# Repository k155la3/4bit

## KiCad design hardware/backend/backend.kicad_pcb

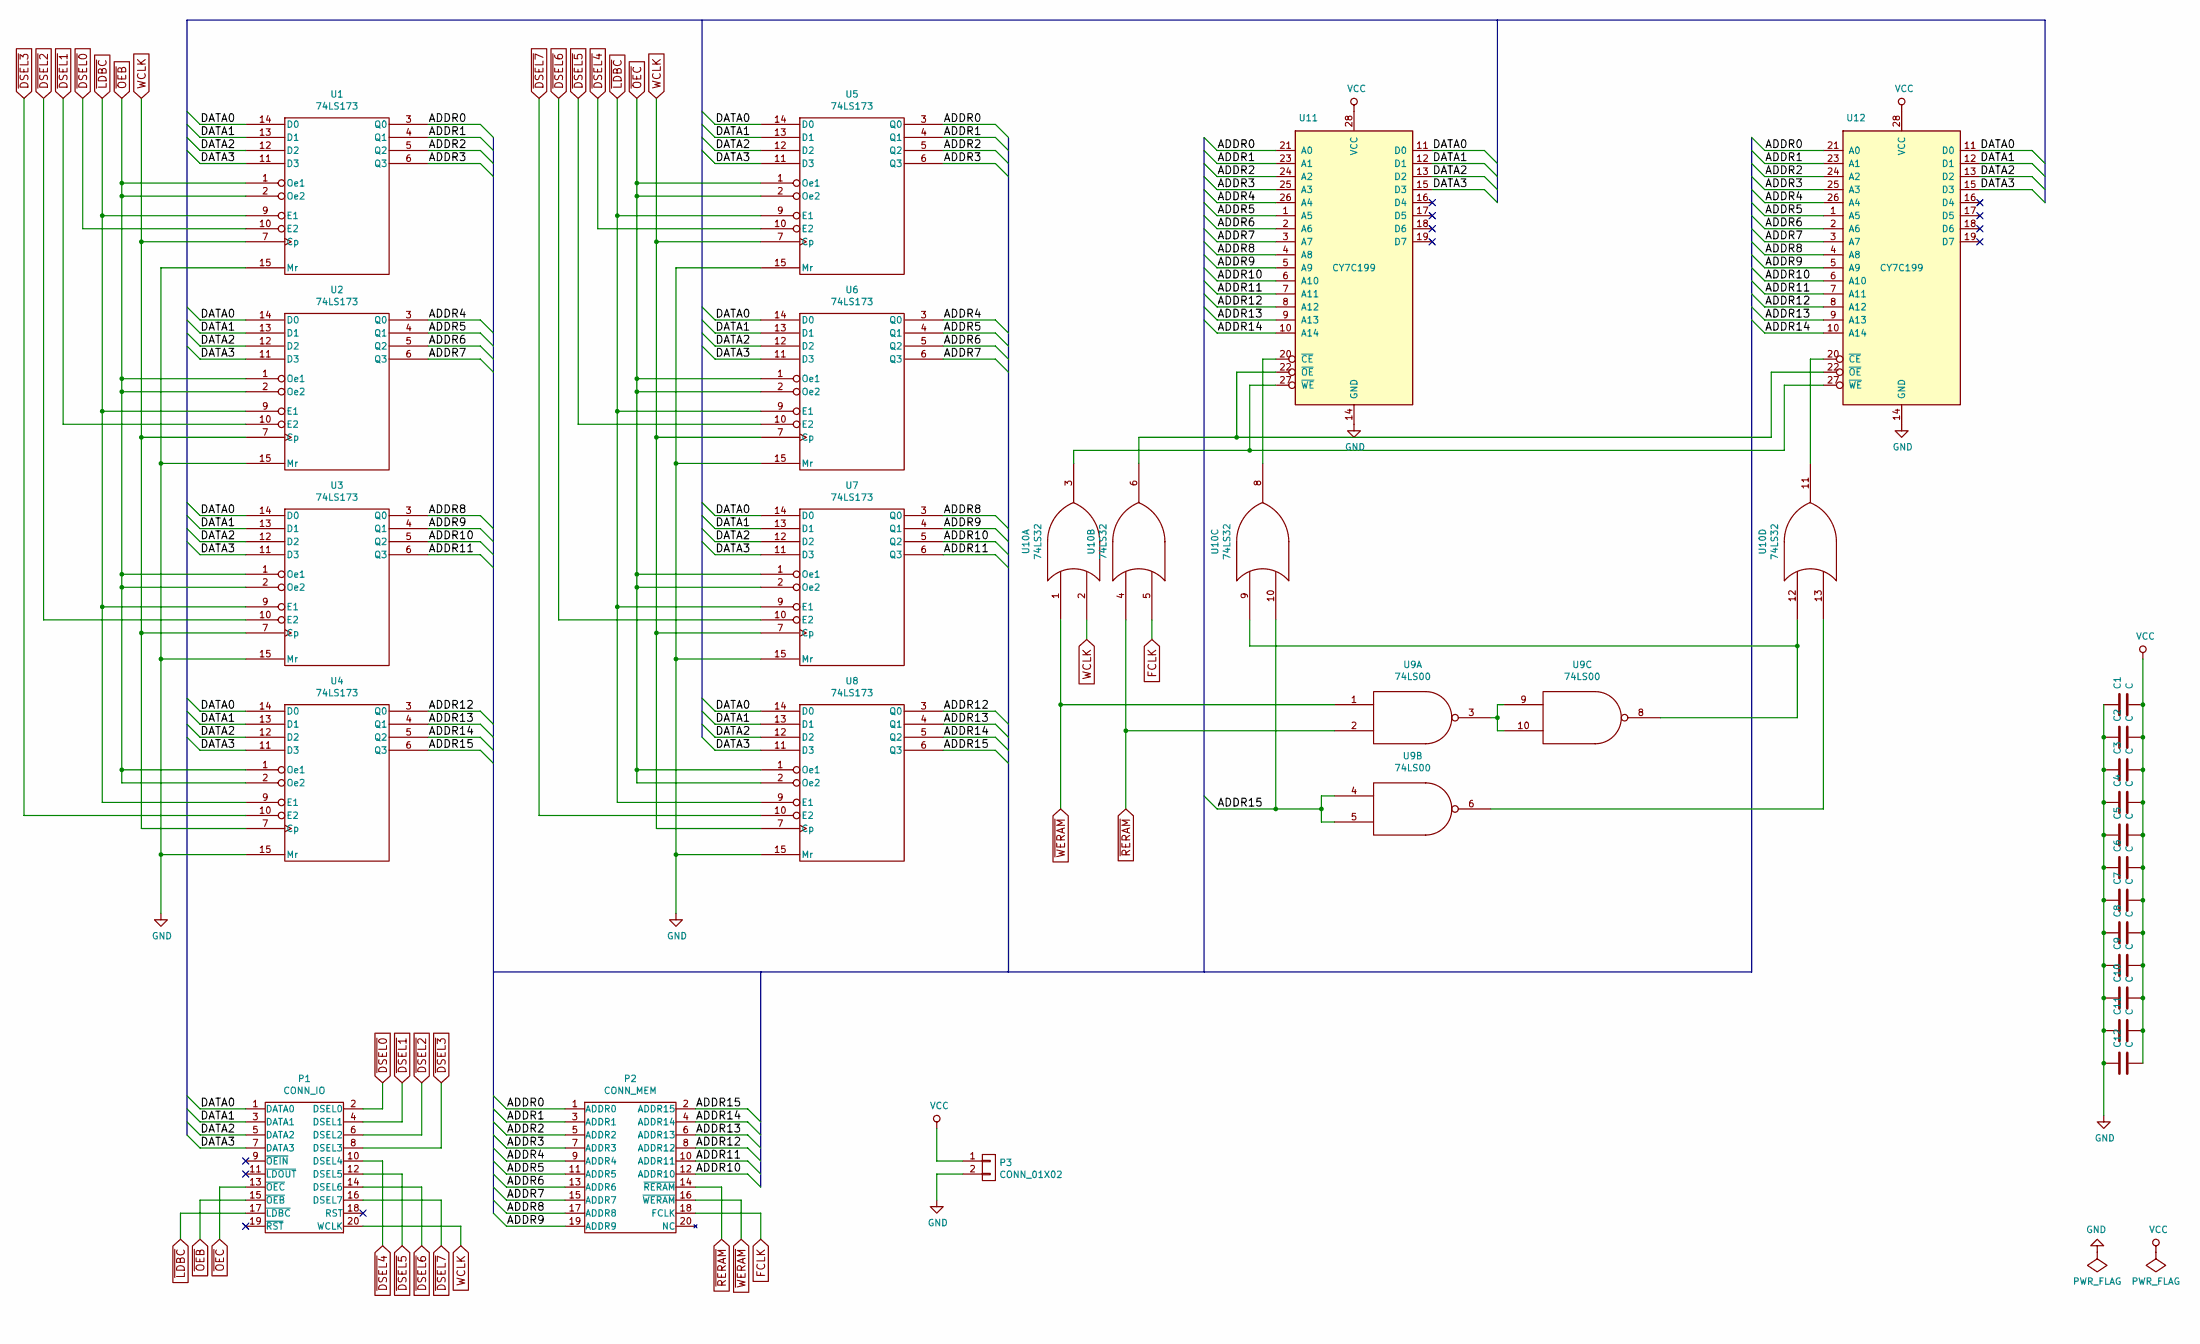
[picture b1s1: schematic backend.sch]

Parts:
C1, C2, C3, C4, C5, C6, C7, C8, C9, C10, C11, C12: C; C_Disc_D3_P2.5
P1: CONN_IO; Socket_Strip_Straight_2x10
P2: CONN_MEM; Socket_Strip_Straight_2x10
P3: CONN_01X02; Pin_Header_Straight_1x02
U1, U2, U3, U4, U5, U6, U7, U8: 74LS173; DIP-16_W7.62mm
U9: 74LS00; DIP-14_W7.62mm
U10: 74LS32; DIP-14_W7.62mm
U11, U12: CY7C199; DIP-28_W7.62mm

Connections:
/ADDR0: P2.1 (ADDR0), U1.3 (Q0), U5.3 (Q0), U11.21 (A0), U12.21 (A0)
/ADDR1: P2.3 (ADDR1), U1.4 (Q1), U5.4 (Q1), U11.23 (A1), U12.23 (A1)
/ADDR2: P2.5 (ADDR2), U1.5 (Q2), U5.5 (Q2), U11.24 (A2), U12.24 (A2)
/ADDR3: P2.7 (ADDR3), U1.6 (Q3), U5.6 (Q3), U11.25 (A3), U12.25 (A3)
/ADDR4: P2.9 (ADDR4), U2.3 (Q0), U6.3 (Q0), U11.26 (A4), U12.26 (A4)
/ADDR5: P2.11 (ADDR5), U2.4 (Q1), U6.4 (Q1), U11.1 (A5), U12.1 (A5)
/ADDR6: P2.13 (ADDR6), U2.5 (Q2), U6.5 (Q2), U11.2 (A6), U12.2 (A6)
/ADDR7: P2.15 (ADDR7), U2.6 (Q3), U6.6 (Q3), U11.3 (A7), U12.3 (A7)
/ADDR8: P2.17 (ADDR8), U3.3 (Q0), U7.3 (Q0), U11.4 (A8), U12.4 (A8)
/ADDR9: P2.19 (ADDR9), U3.4 (Q1), U7.4 (Q1), U11.5 (A9), U12.5 (A9)
/ADDR10: P2.12 (ADDR10), U3.5 (Q2), U7.5 (Q2), U11.6 (A10), U12.6 (A10)
/ADDR11: P2.10 (ADDR11), U3.6 (Q3), U7.6 (Q3), U11.7 (A11), U12.7 (A11)
/ADDR12: P2.8 (ADDR12), U4.3 (Q0), U8.3 (Q0), U11.8 (A12), U12.8 (A12)
/ADDR13: P2.6 (ADDR13), U4.4 (Q1), U8.4 (Q1), U11.9 (A13), U12.9 (A13)
/ADDR14: P2.4 (ADDR14), U4.5 (Q2), U8.5 (Q2), U11.10 (A14), U12.10 (A14)
/ADDR15: P2.2 (ADDR15), U4.6 (Q3), U8.6 (Q3), U9.4, U9.5, U10.10
/DATA0: P1.1 (DATA0), U1.14 (D0), U2.14 (D0), U3.14 (D0), U4.14 (D0), U5.14 (D0), U6.14 (D0), U7.14 (D0), U8.14 (D0), U11.11 (D0), U12.11 (D0)
/DATA1: P1.3 (DATA1), U1.13 (D1), U2.13 (D1), U3.13 (D1), U4.13 (D1), U5.13 (D1), U6.13 (D1), U7.13 (D1), U8.13 (D1), U11.12 (D1), U12.12 (D1)
/DATA2: P1.5 (DATA2), U1.12 (D2), U2.12 (D2), U3.12 (D2), U4.12 (D2), U5.12 (D2), U6.12 (D2), U7.12 (D2), U8.12 (D2), U11.13 (D2), U12.13 (D2)
/DATA3: P1.7 (DATA3), U1.11 (D3), U2.11 (D3), U3.11 (D3), U4.11 (D3), U5.11 (D3), U6.11 (D3), U7.11 (D3), U8.11 (D3), U11.15 (D3), U12.15 (D3)
FCLK: P2.18 (FCLK), U10.5
GND: C1.1, C2.1, C3.1, C4.1, C5.1, C6.1, C7.1, C8.1, C9.1, C10.1, C11.1, C12.1, P3.2, U1.8 (GND), U1.15 (Mr), U2.8 (GND), U2.15 (Mr), U3.8 (GND), U3.15 (Mr), U4.8 (GND), U4.15 (Mr), U5.8 (GND), U5.15 (Mr), U6.8 (GND), U6.15 (Mr), U7.8 (GND), U7.15 (Mr), U8.8 (GND), U8.15 (Mr), U9.7 (GND), U10.7 (GND), U11.14 (GND), U12.14 (GND)
unnamed: U9.3, U9.9, U9.10
unnamed: U10.3, U11.27 (~WE~), U12.27 (~WE~)
unnamed: U10.6, U11.22 (~OE~), U12.22 (~OE~)
unnamed: U10.8, U11.20 (~CE~)
unnamed: U10.11, U12.20 (~CE~)
unnamed: U9.8, U10.9, U10.12
unnamed: U9.6, U10.13
VCC: C1.2, C2.2, C3.2, C4.2, C5.2, C6.2, C7.2, C8.2, C9.2, C10.2, C11.2, C12.2, P3.1, U1.16 (VCC), U2.16 (VCC), U3.16 (VCC), U4.16 (VCC), U5.16 (VCC), U6.16 (VCC), U7.16 (VCC), U8.16 (VCC), U9.14 (VCC), U10.14 (VCC), U11.28 (VCC), U12.28 (VCC)
WCLK: P1.20 (WCLK), U1.7 (Cp), U2.7 (Cp), U3.7 (Cp), U4.7 (Cp), U5.7 (Cp), U6.7 (Cp), U7.7 (Cp), U8.7 (Cp), U10.2
~DSEL0: P1.2 (DSEL0), U1.10 (E2)
~DSEL1: P1.4 (DSEL1), U2.10 (E2)
~DSEL2: P1.6 (DSEL2), U3.10 (E2)
~DSEL3: P1.8 (DSEL3), U4.10 (E2)
~DSEL4: P1.10 (DSEL4), U5.10 (E2)
~DSEL5: P1.12 (DSEL5), U6.10 (E2)
~DSEL6: P1.14 (DSEL6), U7.10 (E2)
~DSEL7: P1.16 (DSEL7), U8.10 (E2)
~LDBC: P1.17 (~LDBC), U1.9 (E1), U2.9 (E1), U3.9 (E1), U4.9 (E1), U5.9 (E1), U6.9 (E1), U7.9 (E1), U8.9 (E1)
~OEB: P1.15 (~OEB), U1.1 (Oe1), U1.2 (Oe2), U2.1 (Oe1), U2.2 (Oe2), U3.1 (Oe1), U3.2 (Oe2), U4.1 (Oe1), U4.2 (Oe2)
~OEC: P1.13 (~OEC), U5.1 (Oe1), U5.2 (Oe2), U6.1 (Oe1), U6.2 (Oe2), U7.1 (Oe1), U7.2 (Oe2), U8.1 (Oe1), U8.2 (Oe2)
~RERAM: P2.14 (~RERAM), U9.2, U10.4
~WERAM: P2.16 (~WERAM), U9.1, U10.1

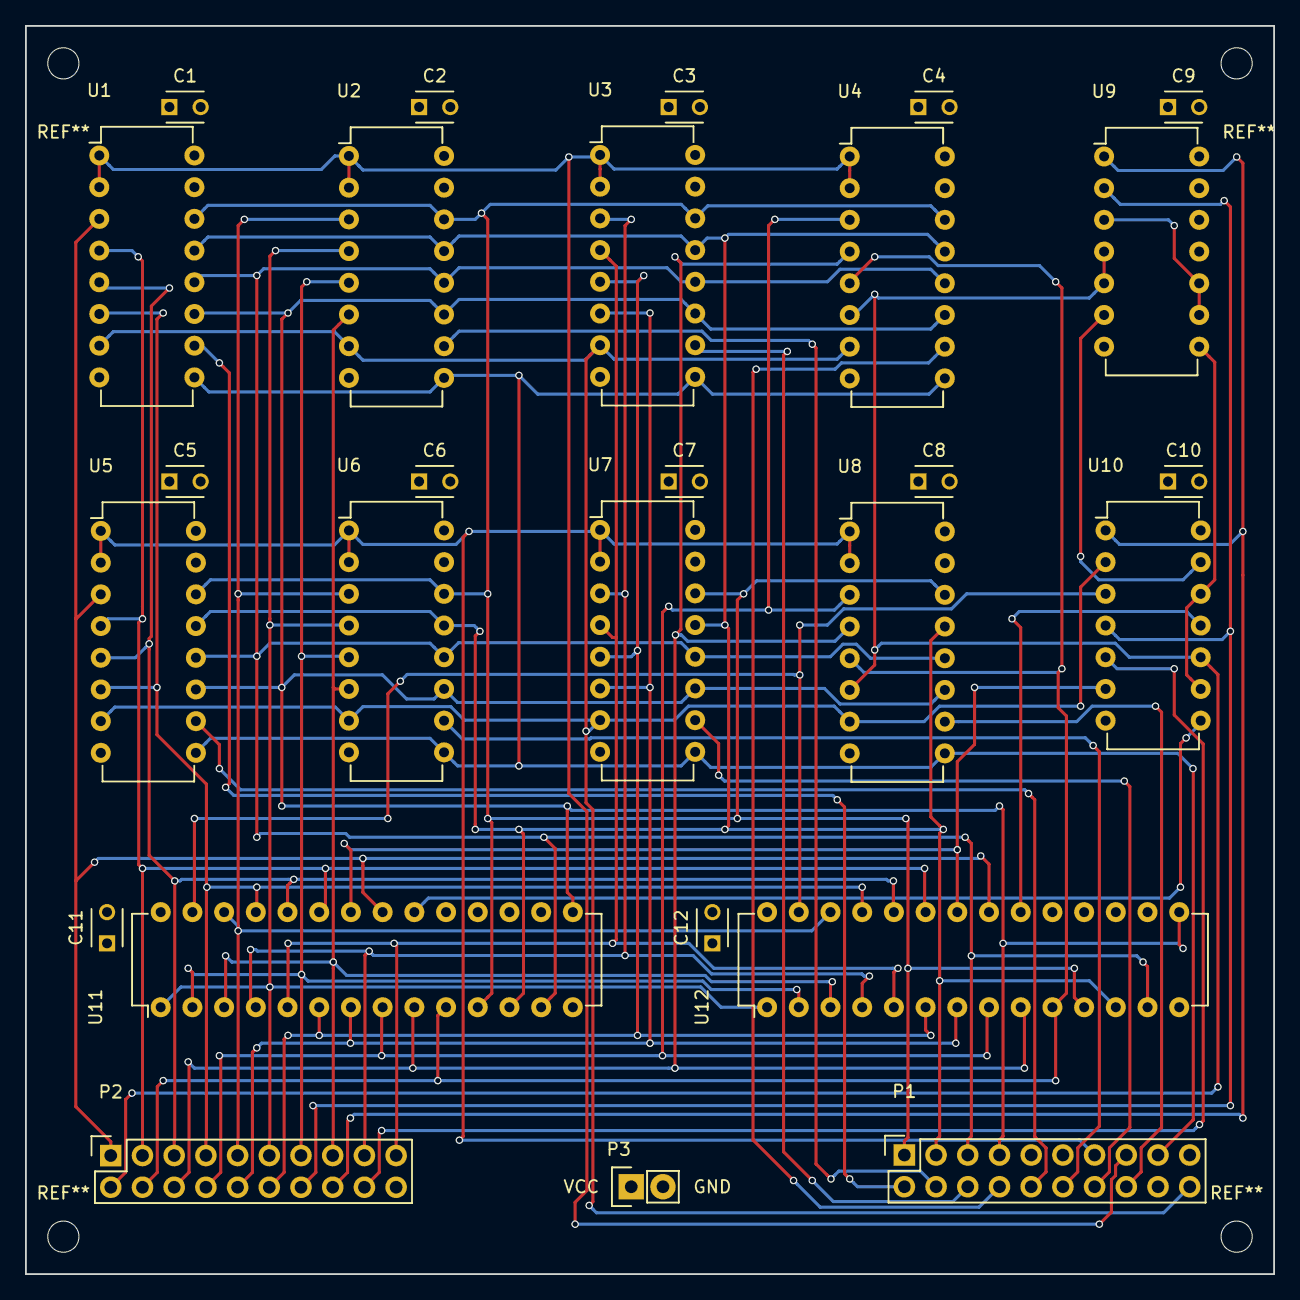
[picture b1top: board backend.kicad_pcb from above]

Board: 4 copper layers, 100.0 x 100.0 mm, 27 parts (0 on the bottom side), 44 nets.

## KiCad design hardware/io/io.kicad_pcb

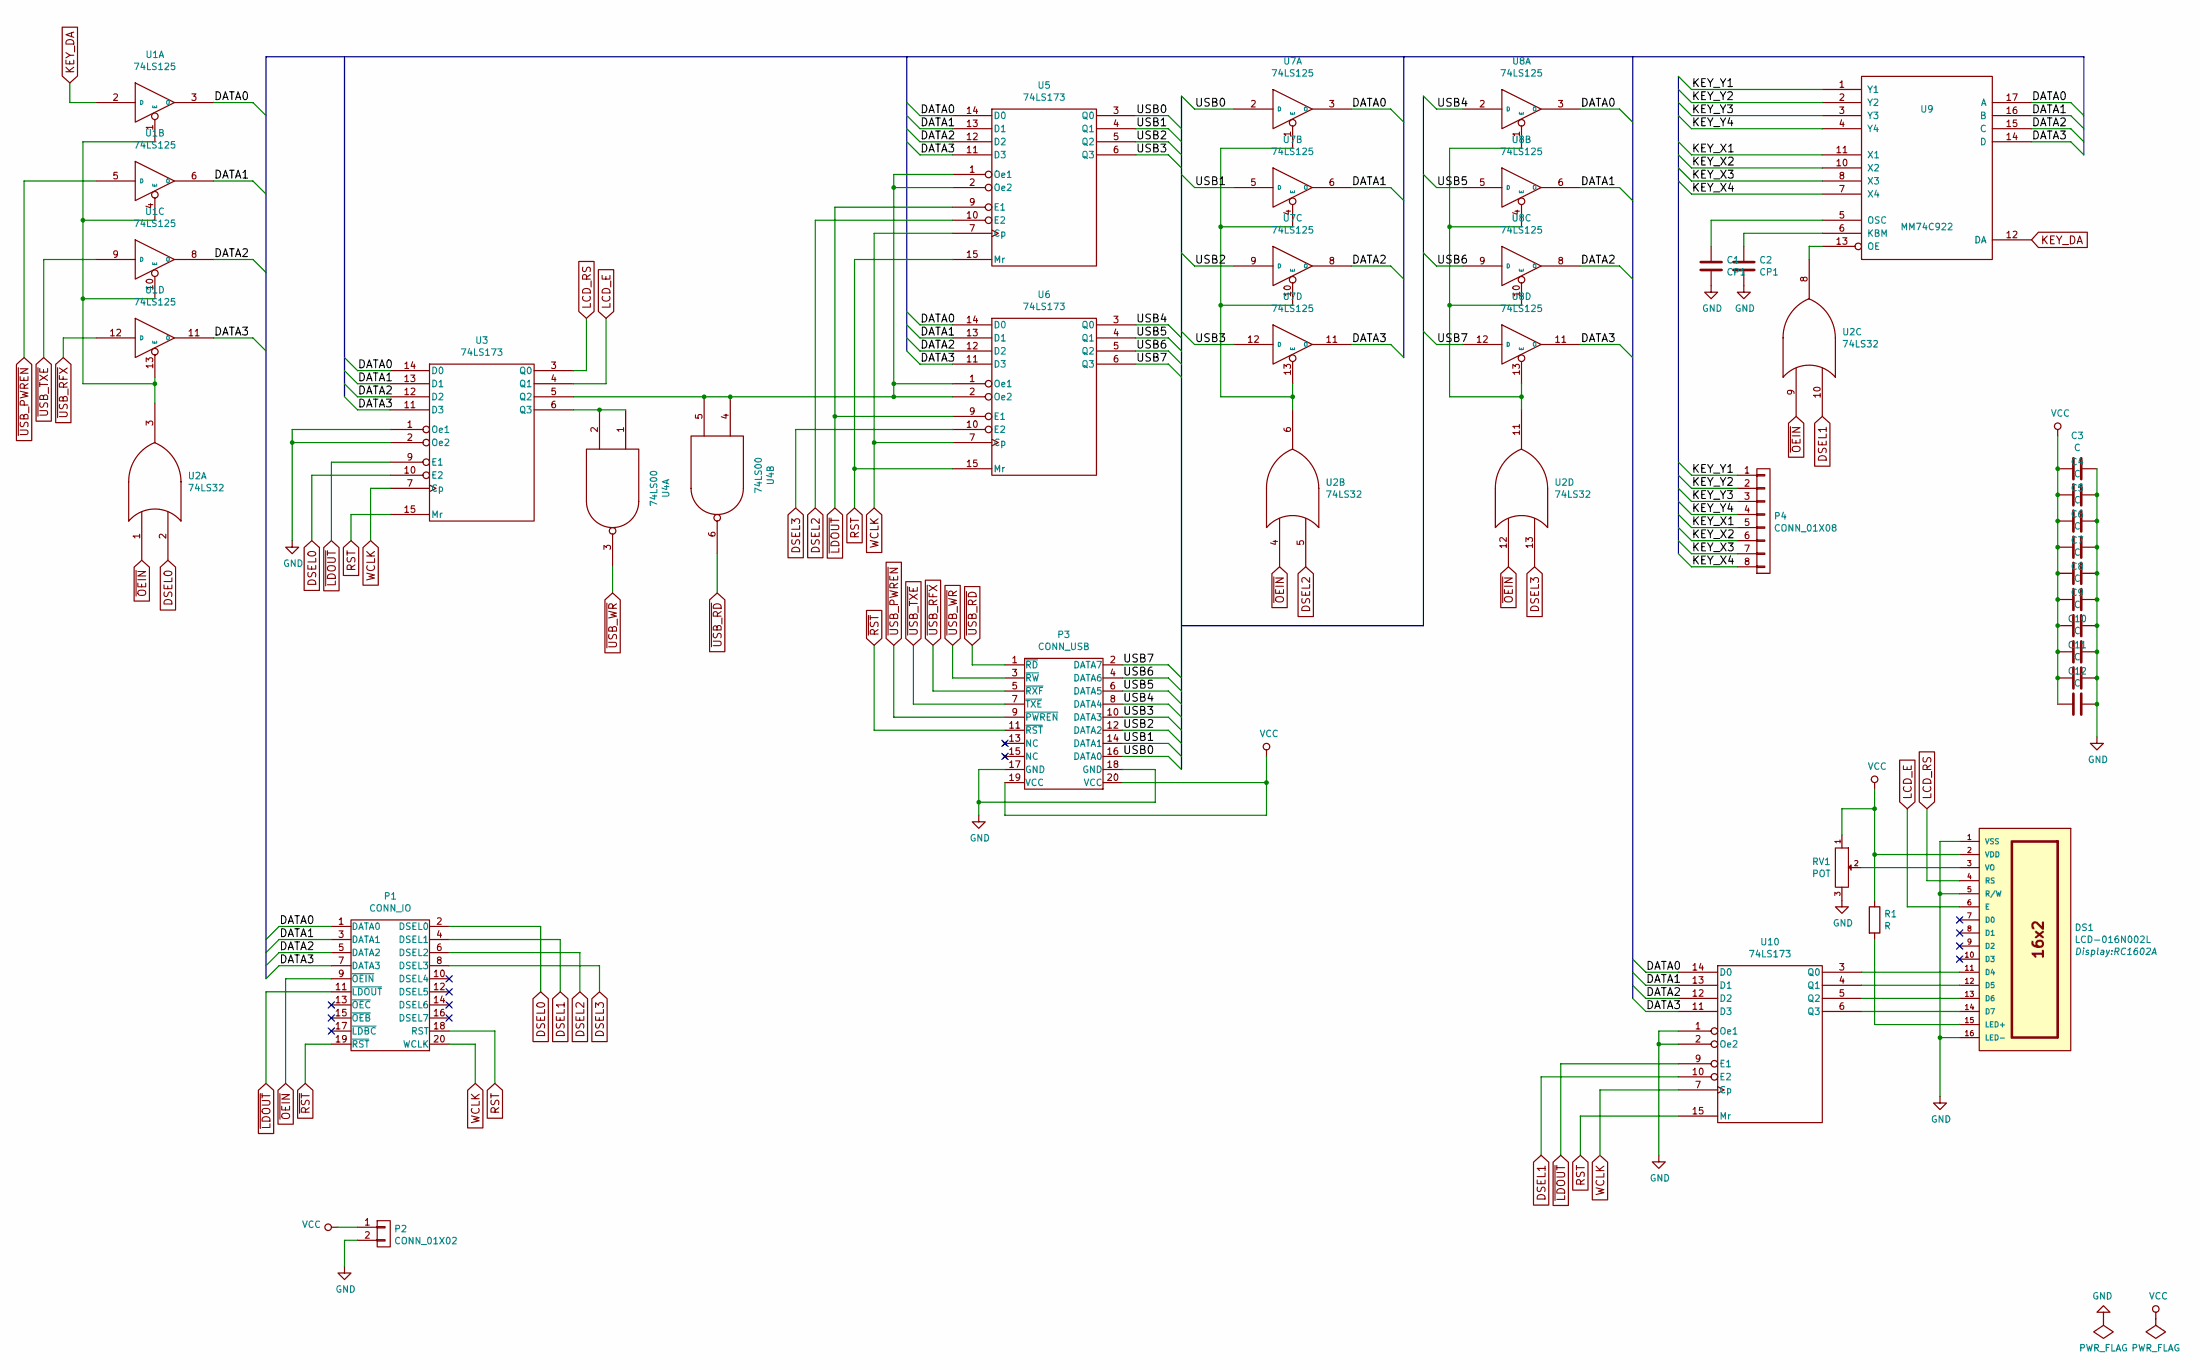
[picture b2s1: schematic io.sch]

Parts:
C1: CP1; C_Disc_D6_P5
C2: CP1; C_Disc_D3_P2.5
C3, C4, C5, C6, C7, C8, C9, C10, C11, C12: C; C_Disc_D3_P2.5
DS1: LCD-016N002L; RC1602A
P1: CONN_IO; Socket_Strip_Straight_2x10
P2: CONN_01X02; Pin_Header_Straight_1x02
P3: CONN_USB; Socket_Strip_Straight_2x10
P4: CONN_01X08; Pin_Header_Straight_1x08
R1: R; Resistor_Horizontal_RM10mm
RV1: POT; Potentiometer_Trimmer-Suntan-TSR-3386P
U1, U7, U8: 74LS125; DIP-14_W7.62mm
U2: 74LS32; DIP-14_W7.62mm
U3, U5, U6, U10: 74LS173; DIP-16_W7.62mm
U4: 74LS00; DIP-14_W7.62mm
U9: MM74C922; DIP-18_W7.62mm

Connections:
/DATA0: P1.1 (DATA0), U1.3 (O), U3.14 (D0), U5.14 (D0), U6.14 (D0), U7.3 (O), U8.3 (O), U9.17 (A), U10.14 (D0)
/DATA1: P1.3 (DATA1), U1.6 (O), U3.13 (D1), U5.13 (D1), U6.13 (D1), U7.6 (O), U8.6 (O), U9.16 (B), U10.13 (D1)
/DATA2: P1.5 (DATA2), U1.8 (O), U3.12 (D2), U5.12 (D2), U6.12 (D2), U7.8 (O), U8.8 (O), U9.15 (C), U10.12 (D2)
/DATA3: P1.7 (DATA3), U1.11 (O), U3.11 (D3), U5.11 (D3), U6.11 (D3), U7.11 (O), U8.11 (O), U9.14 (D), U10.11 (D3)
/KEY_X1: P4.5, U9.11 (X1)
/KEY_X2: P4.6, U9.10 (X2)
/KEY_X3: P4.7, U9.8 (X3)
/KEY_X4: P4.8, U9.7 (X4)
/KEY_Y1: P4.1, U9.1 (Y1)
/KEY_Y2: P4.2, U9.2 (Y2)
/KEY_Y3: P4.3, U9.3 (Y3)
/KEY_Y4: P4.4, U9.4 (Y4)
/USB0: P3.16 (DATA0), U5.3 (Q0), U7.2 (D)
/USB1: P3.14 (DATA1), U5.4 (Q1), U7.5 (D)
/USB2: P3.12 (DATA2), U5.5 (Q2), U7.9 (D)
/USB3: P3.10 (DATA3), U5.6 (Q3), U7.12 (D)
/USB4: P3.8 (DATA4), U6.3 (Q0), U8.2 (D)
/USB5: P3.6 (DATA5), U6.4 (Q1), U8.5 (D)
/USB6: P3.4 (DATA6), U6.5 (Q2), U8.9 (D)
/USB7: P3.2 (DATA7), U6.6 (Q3), U8.12 (D)
DSEL0: P1.2 (DSEL0), U2.2, U3.10 (E2)
DSEL1: P1.4 (DSEL1), U2.10, U10.10 (E2)
DSEL2: P1.6 (DSEL2), U2.5, U5.10 (E2)
DSEL3: P1.8 (DSEL3), U2.13, U6.10 (E2)
GND: C1.2, C2.2, C3.1, C4.1, C5.1, C6.1, C7.1, C8.1, C9.1, C10.1, C11.1, C12.1, DS1.1 (VSS), DS1.5 (R/W), DS1.16 (LED-), P2.2, P3.17 (GND), P3.18 (GND), RV1.3, U1.7 (GND), U2.7 (GND), U3.1 (Oe1), U3.2 (Oe2), U3.8 (GND), U4.7 (GND), U5.8 (GND), U6.8 (GND), U7.7 (GND), U8.7 (GND), U9.9 (GND), U10.1 (Oe1), U10.2 (Oe2), U10.8 (GND)
KEY_DA: U1.2 (D), U9.12 (DA)
LCD_E: DS1.6 (E), U3.4 (Q1)
LCD_RS: DS1.4 (RS), U3.3 (Q0)
unnamed: C1.1, U9.5 (OSC)
unnamed: C2.1, U9.6 (KBM)
unnamed: DS1.3 (VO), RV1.2
unnamed: DS1.11 (D4), U10.3 (Q0)
unnamed: DS1.12 (D5), U10.4 (Q1)
unnamed: DS1.13 (D6), U10.5 (Q2)
unnamed: DS1.14 (D7), U10.6 (Q3)
unnamed: DS1.15 (LED+), R1.2
unnamed: U1.1 (E), U1.4 (E), U1.10 (E), U1.13 (E), U2.3
unnamed: U2.6, U7.1 (E), U7.4 (E), U7.10 (E), U7.13 (E)
unnamed: U2.8, U9.13 (OE)
unnamed: U2.11, U8.1 (E), U8.4 (E), U8.10 (E), U8.13 (E)
unnamed: U3.5 (Q2), U4.4, U4.5, U5.1 (Oe1), U5.2 (Oe2), U6.1 (Oe1), U6.2 (Oe2)
unnamed: U3.6 (Q3), U4.1, U4.2
RST: P1.18 (RST), U3.15 (Mr), U5.15 (Mr), U6.15 (Mr), U10.15 (Mr)
VCC: C3.2, C4.2, C5.2, C6.2, C7.2, C8.2, C9.2, C10.2, C11.2, C12.2, DS1.2 (VDD), P2.1, P3.19 (VCC), P3.20 (VCC), R1.1, RV1.1, U1.14 (VCC), U2.14 (VCC), U3.16 (VCC), U4.14 (VCC), U5.16 (VCC), U6.16 (VCC), U7.14 (VCC), U8.14 (VCC), U9.18 (VCC), U10.16 (VCC)
WCLK: P1.20 (WCLK), U3.7 (Cp), U5.7 (Cp), U6.7 (Cp), U10.7 (Cp)
~LDOUT: P1.11 (~LDOUT), U3.9 (E1), U5.9 (E1), U6.9 (E1), U10.9 (E1)
~OEIN: P1.9 (~OEIN), U2.1, U2.4, U2.9, U2.12
~RST: P1.19 (~RST), P3.11 (~RST)
~USB_PWREN: P3.9 (~PWREN), U1.5 (D)
~USB_RD: P3.1 (~RD), U4.6
~USB_RFX: P3.5 (~RXF), U1.12 (D)
~USB_TXE: P3.7 (~TXE), U1.9 (D)
~USB_WR: P3.3 (~RW), U4.3

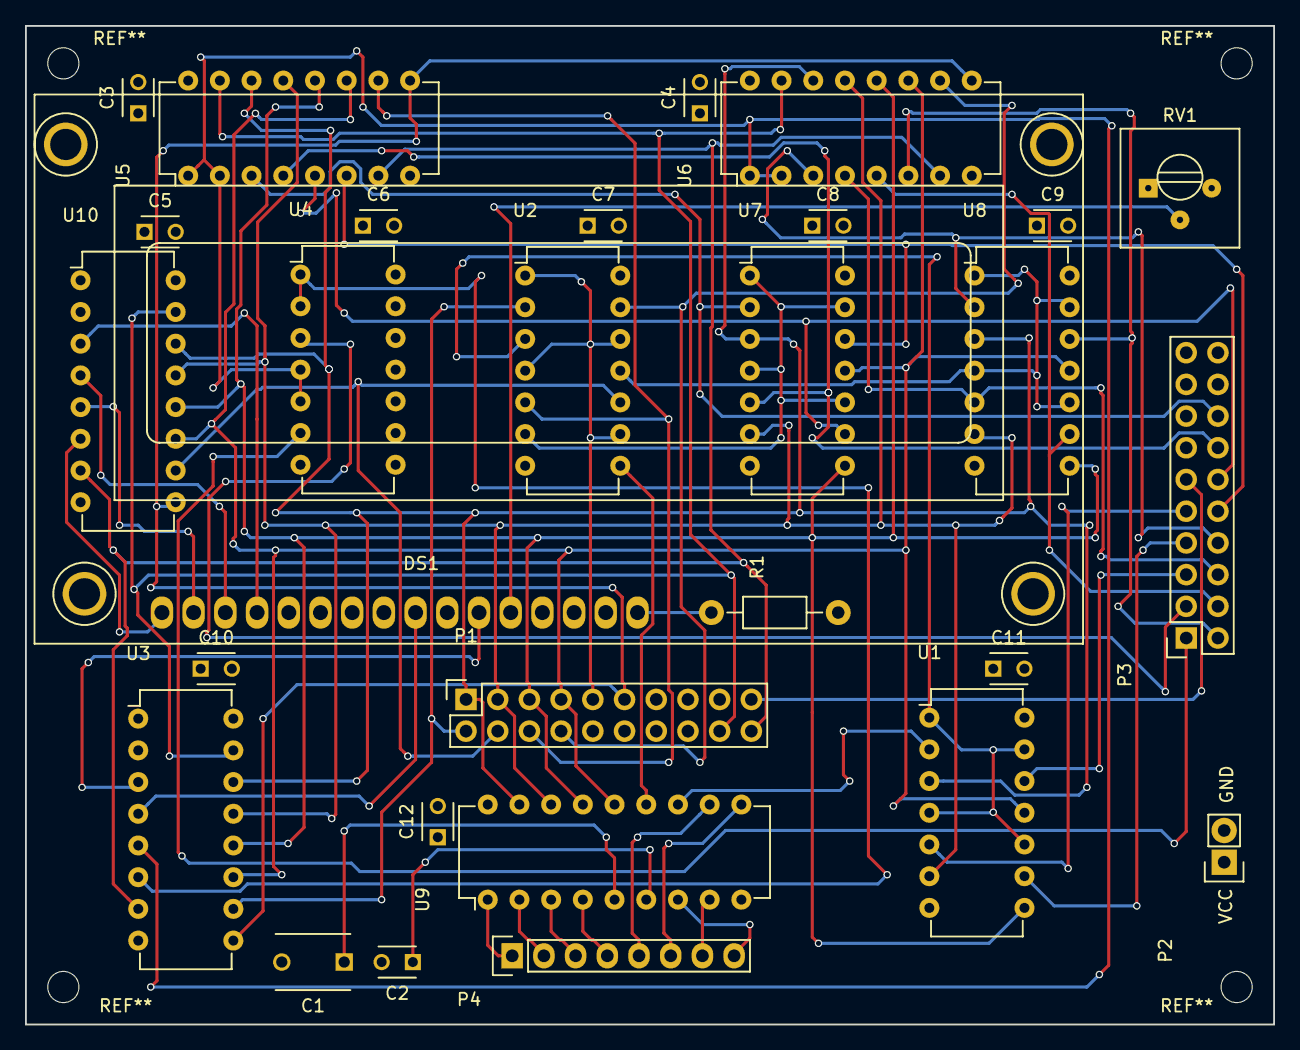
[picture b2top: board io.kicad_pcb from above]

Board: 4 copper layers, 100.0 x 80.0 mm, 29 parts (0 on the bottom side), 53 nets.

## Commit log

2015-11-03 Initial
2015-11-08 ALU-WIP
2015-11-08 Hardware--WIP
2015-11-09 Schematics--WIP
2015-11-09 Compact ucode generator. Fixed step simulation. Assembler for ALU.
2015-11-09 Move files
2015-11-13 Separate write scripts for ucode0/1
2015-11-13 ALU schematics
2015-11-13 CSV simulator trace
2015-11-15 Fix width IS--WIP
2015-11-15 Jump machine
2015-11-21 Verified ucode from TSV source
2015-11-22 New simulator. Pipe through asm/simu. Fix ucode.
2015-11-22 Name declarations
2015-11-22 Clarify asm passes
2015-11-23 Ucode write script
2015-11-23 Macro assembler, Fix simulator.
2015-11-24 Simulate memory
2015-11-24 Assembler allocations
2015-11-24 Test jump machine
2015-11-25 Fix to get zero flag from ALU result directly. Fix NOR simulation.
2015-11-25 Fix for macro with literal args
2015-11-25 Test ALU
2015-11-26 Change ALU instructions to use C
2015-11-26 Fix ALU CROUT
2015-11-26 Test RAM--WIP
2015-11-27 Assembler: macro namespaced definitions; main macro; multiple input files
2015-11-28 Assembler: symbols
2015-11-28 Simulator: debugger
2015-11-28 Library macro naming convention
2015-11-28 Buzzer
2015-11-30 Update schematics
2015-12-03 Schematics for common SEL decoder
2015-12-03 SEL uCode
2015-12-04 Fix uCode
2015-12-04 Adjust mnemonics
2015-12-04 Change simulator to support SEL and ~LDALU
2015-12-07 Support ROR
2015-12-07 Fix ~LDFL handling. Fix ROR.
2015-12-08 Generic object writer
2015-12-16 New micro-code
2015-12-16 Adjust for IS changes
2015-12-16 Reorganize files
2015-12-23 WERAM/RERAM signals. Clean simulator machine cycle.
2015-12-29 Various tests
2015-12-31 Test USB echo
2016-01-06 Test keypad/screen
2016-01-08 Multipart macros. Allow external definition scopes.
2016-01-08 Integrated test
2016-01-08 Add .gitignore
2016-01-09 Main lib and call/ret. Assembler to support char literals and offset.
2016-01-17 Support steping into macro without running machine. Virtual __end label.
2016-01-17 Use __end label
2016-01-17 Fix offset
2016-01-17 Probe out ports
2016-01-17 Test USB
2016-01-18 Keypad test
2016-01-18 Remove old tests
2016-01-23 Debugger introspection into defs/maps. Label on own line.
2016-01-28 Schematics
2016-01-31 IO board
2016-02-01 OSH Park production Gerber prep
2016-02-01 Supply ~RST to USB interface
2016-02-20 Adjust for changes in IO control word
2016-02-20 Frontend--WIP
2016-02-21 Run system tests before USB test
2016-02-22 Use 32K EEPROM
2016-03-04 Backend hardware
2016-03-04 Changes in IO hardware
2016-04-05 Support B3/C3 registers
2016-04-05 Backend PCB
2016-06-17 Fix for B3/C3 registers
2016-06-17 Fix for older node
2016-06-17 Adjust for large RAM. Fix for faulty 0 cycle.
2016-06-17 Remove extra tests from USB test
2017-05-28 Verilog--WIP
2017-05-28 Scheme-based asm
2017-05-30 Simplify clock
2017-06-03 Verilog ALU and IN/OUT ports
2017-06-03 Fix syntax
2017-06-03 Add IN/OUT ports to test bench
2017-06-08 Simulate IO
2017-06-09 Echo IO
2017-06-09 Echo via RAM
2017-06-09 Parametrize RAM
2017-06-09 Parametrize register and counter
2017-06-12 V2 ucode
2017-06-12 Feed data bus directly from A to avoid combinatorial loops
2017-06-14 FT245R simulation
2017-06-14 Removed unused control
2017-06-16 Generate data file
2017-06-16 Echo on Arty
2017-06-17 Load flags only for ADD, CMP and NOR. Carry in for ADD.
2017-06-17 Update ucode
2017-06-18 Remove hint
2017-06-18 Clocked reads to enable BRAM
2017-06-18 Parametrize prog ROM file. Connect LEDs only.
2017-06-18 Additional config
2017-06-18 32-bit octo literal
2017-06-18 Store/add library
2017-06-19 Phased clock
2017-06-19 Two clocks
2017-06-21 Generate clock
2017-06-21 Verilator clock
2017-07-12 Pipeline--WIP
2017-10-08 Counter program
2017-10-17 UART interface and its simulation
2017-10-24 Hello world!
2017-10-24 Wait for input before print
